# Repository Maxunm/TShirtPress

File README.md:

# See [Rumel.IO](https://www.rumel.io/2019/11/05/T-Shirt-Press/)

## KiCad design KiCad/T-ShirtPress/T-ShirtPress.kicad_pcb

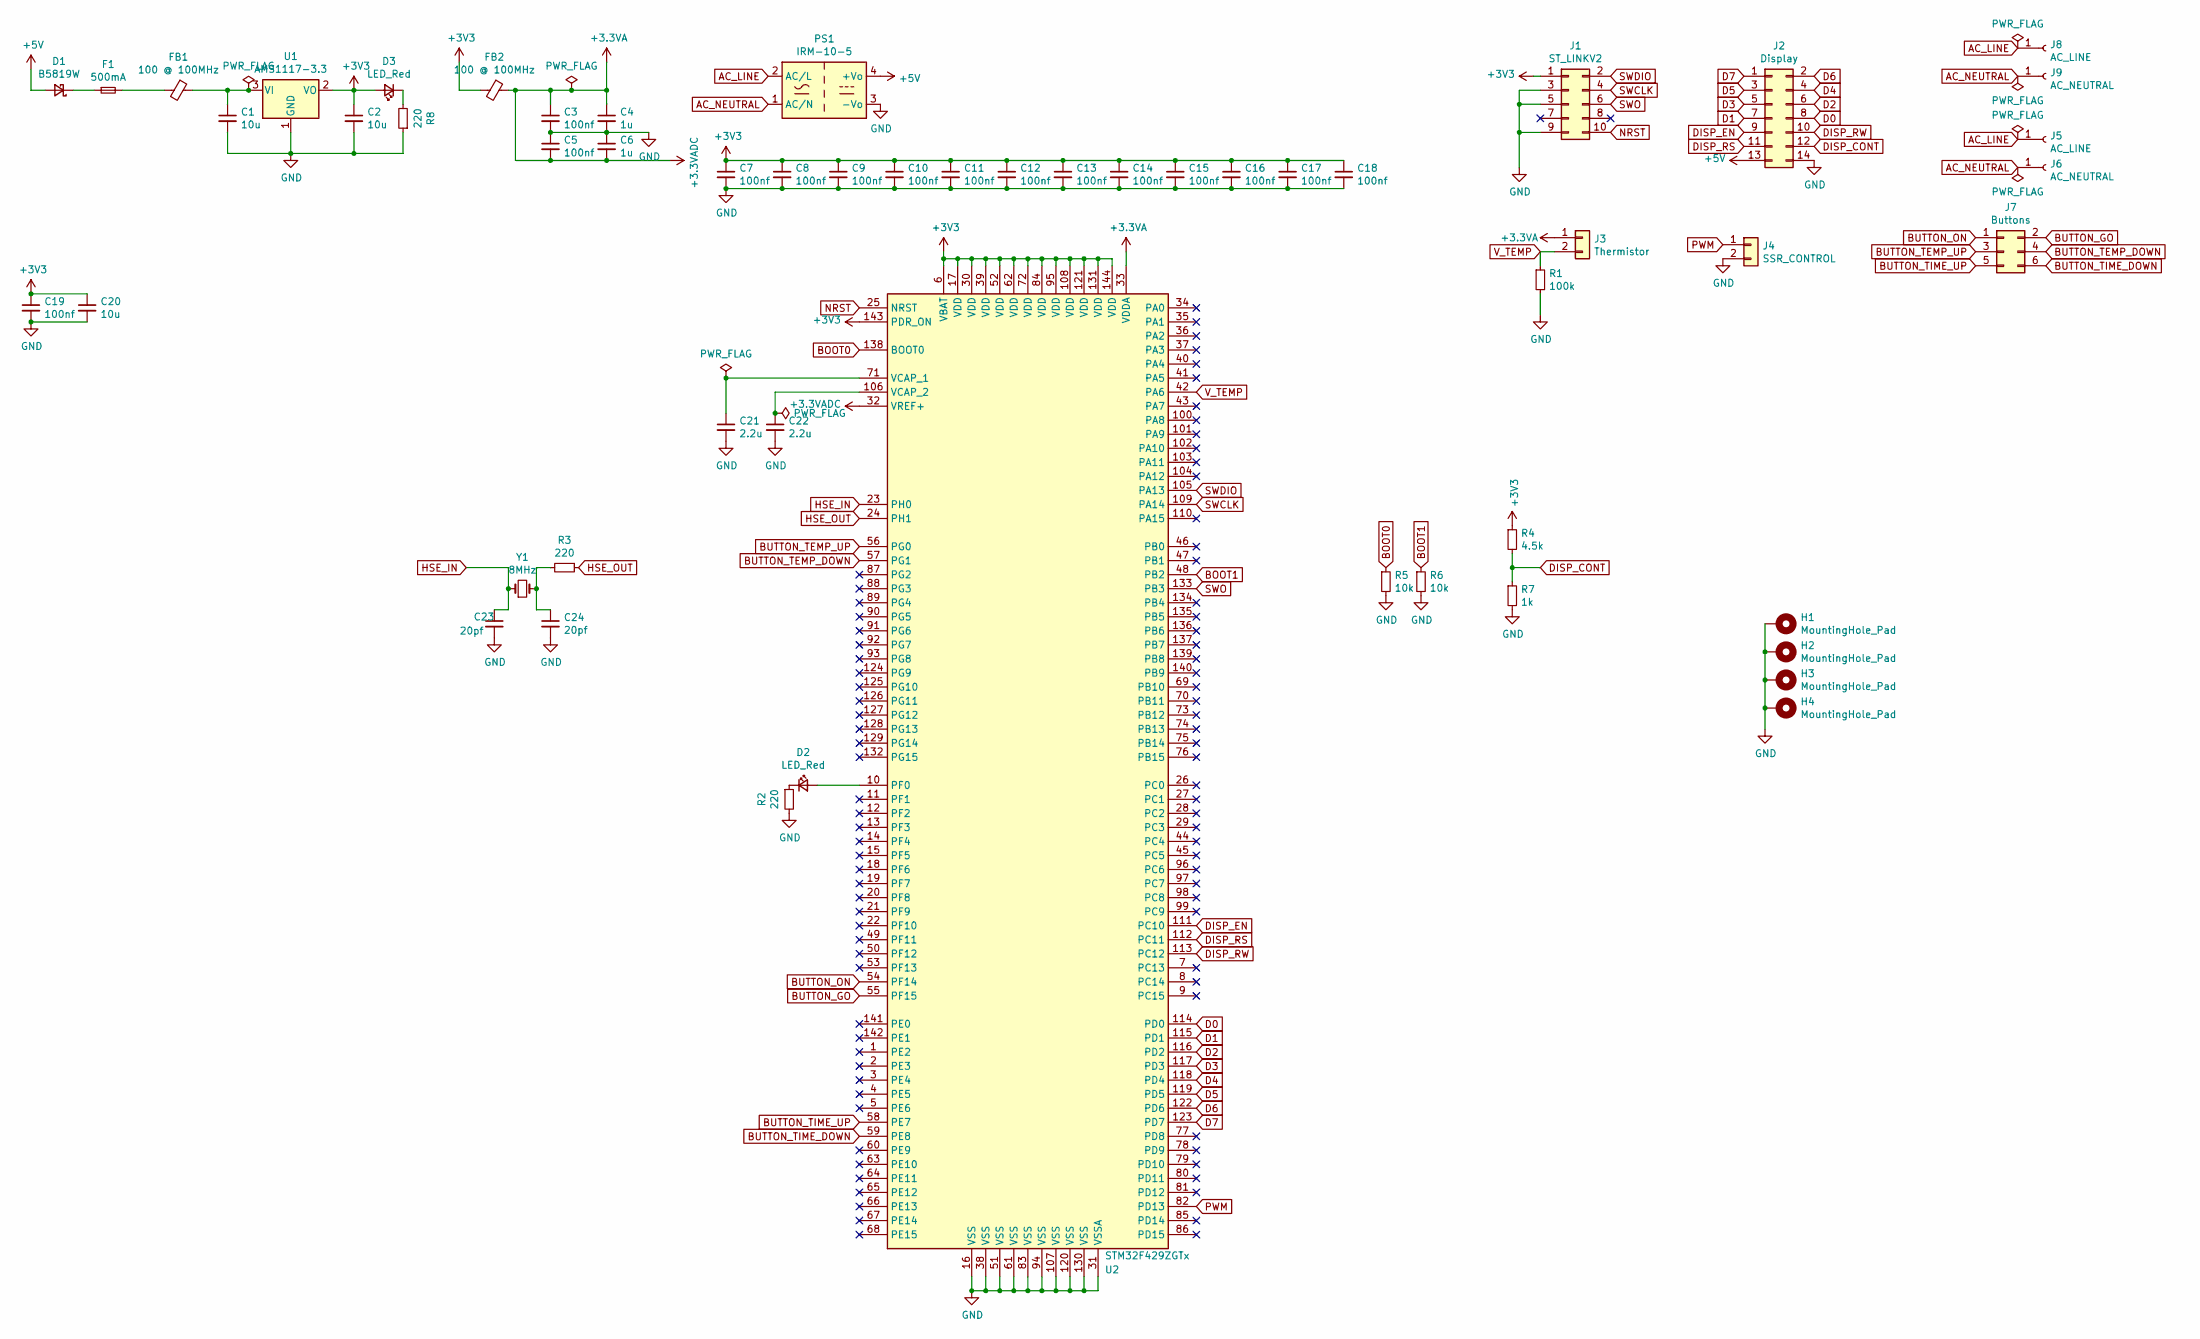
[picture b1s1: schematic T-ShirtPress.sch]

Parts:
C1, C2: 10u; C_0805_2012Metric
C3, C5, C7, C8, C9, C10, C11, C12, C13, C14, C15, C16, C17, C18, C19: 100nf; C_0402_1005Metric
C4, C6: 1u; C_0402_1005Metric
C20: 10u; C_0603_1608Metric
C21, C22: 2.2u; C_0603_1608Metric
C23, C24: 20pf; C_0402_1005Metric
D1: B5819W; D_SOD-123
D2, D3: LED_Red; LED_0603_1608Metric
F1: 500mA; Fuse_1206_3216Metric
FB1, FB2: 100 @ 100MHz; L_0805_2012Metric
H1, H2, H3, H4: MountingHole_Pad; MountingHole_4mm_Pad_Via
J1: ST_LINKV2; PinHeader_2x05_P1.27mm_Vertical_SMD
J2: Display; PinHeader_2x07_P2.54mm_Vertical
J3: Thermistor; JST_EH_B2B-EH-A_1x02_P2.50mm_Vertical
J4: SSR_CONTROL; JST_EH_B2B-EH-A_1x02_P2.50mm_Vertical
J5, J8: AC_LINE; SolderWire-2.5sqmm_1x01_D2.4mm_OD3.6mm
J6, J9: AC_NEUTRAL; SolderWire-2.5sqmm_1x01_D2.4mm_OD3.6mm
J7: Buttons; PinHeader_2x03_P2.54mm_Vertical
PS1: IRM-10-5; Converter_ACDC_MeanWell_IRM-10-xx_THT
R1: 100k; R_0805_2012Metric
R2, R3, R8: 220; R_0603_1608Metric
R4: 4.5k; R_Axial_DIN0204_L3.6mm_D1.6mm_P5.08mm_Horizontal
R5, R6: 10k; R_0402_1005Metric
R7: 1k; R_1206_3216Metric
U1: AMS1117-3.3; SOT-223-3_TabPin2
U2: STM32F429ZGTx; LQFP-144_20x20mm_P0.5mm
Y1: 8MHz; Crystal_SMD_5032-2Pin_5.0x3.2mm

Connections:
+3.3VA: C3.1, C4.1, C5.2, C6.2, FB2.1, J3.1, U2.32 (VREF+), U2.33 (VDDA)
+3V3: C2.1, C7.1, C8.1, C9.1, C10.1, C11.1, C12.1, C13.1, C14.1, C15.1, C16.1, C17.1, C18.1, C19.1, C20.1, D3.2 (A), FB2.2, J1.1, R4.1, U1.2 (VO), U2.6 (VBAT), U2.17 (VDD), U2.30 (VDD), U2.39 (VDD), U2.52 (VDD), U2.62 (VDD), U2.72 (VDD), U2.84 (VDD), U2.95 (VDD), U2.108 (VDD), U2.121 (VDD), U2.131 (VDD), U2.143 (PDR_ON), U2.144 (VDD); also elsewhere on the board
+5V: D1.2 (A), J2.13, PS1.4 (+Vo); also elsewhere on the board
AC_LINE: J5.1, J8.1, PS1.2 (AC/L); also elsewhere on the board
AC_NEUTRAL: J6.1, J9.1, PS1.1 (AC/N); also elsewhere on the board
BOOT0: R5.1, U2.138 (BOOT0)
BOOT1: R6.1, U2.48 (PB2)
BUTTON_GO: J7.2, U2.55 (PF15)
BUTTON_ON: J7.1, U2.54 (PF14)
BUTTON_TEMP_DOWN: J7.4, U2.57 (PG1)
BUTTON_TEMP_UP: J7.3, U2.56 (PG0)
BUTTON_TIME_DOWN: J7.6, U2.59 (PE8)
BUTTON_TIME_UP: J7.5, U2.58 (PE7)
D0: J2.8, U2.114 (PD0)
D1: J2.7, U2.115 (PD1)
D2: J2.6, U2.116 (PD2)
D3: J2.5, U2.117 (PD3)
D4: J2.4, U2.118 (PD4)
D5: J2.3, U2.119 (PD5)
D6: J2.2, U2.122 (PD6)
D7: J2.1, U2.123 (PD7)
DISP_CONT: J2.12, R4.2, R7.1
DISP_EN: J2.9, U2.111 (PC10)
DISP_RS: J2.11, U2.112 (PC11)
DISP_RW: J2.10, U2.113 (PC12)
GND: C1.2, C2.2, C3.2, C4.2, C5.1, C6.1, C7.2, C8.2, C9.2, C10.2, C11.2, C12.2, C13.2, C14.2, C15.2, C16.2, C17.2, C18.2, C19.2, C20.2, C21.2, C22.2, C23.2, C24.2, H1.1, H2.1, H3.1, H4.1, J1.3, J1.5, J1.9, J2.14, J4.2, PS1.3 (-Vo), R1.2, R2.2, R5.2, R6.2, R7.2, R8.1, U1.1 (GND), U2.16 (VSS), U2.31 (VSSA), U2.38 (VSS), U2.51 (VSS), U2.61 (VSS), U2.83 (VSS), U2.94 (VSS), U2.107 (VSS), U2.120 (VSS), U2.130 (VSS); also elsewhere on the board
HSE_IN: C23.1, U2.23 (PH0), Y1.1
HSE_OUT: R3.1, U2.24 (PH1)
NRST: J1.10, U2.25 (NRST)
unnamed: C1.1, FB1.1, U1.3 (VI)
unnamed: C21.1, U2.71 (VCAP_1)
unnamed: C22.1, U2.106 (VCAP_2)
unnamed: C24.1, R3.2, Y1.2
unnamed: D1.1 (K), F1.1
unnamed 34: D2.1 (K), R2.1; also elsewhere on the board
unnamed 35: D2.2 (A), U2.10 (PF0); also elsewhere on the board
unnamed 36: D3.1 (K), R8.2; also elsewhere on the board
unnamed: F1.2, FB1.2
PWM: J4.1, U2.82 (PD13)
SWCLK: J1.4, U2.109 (PA14)
SWDIO: J1.2, U2.105 (PA13)
SWO: J1.6, U2.133 (PB3)
V_TEMP: J3.2, R1.1, U2.42 (PA6)

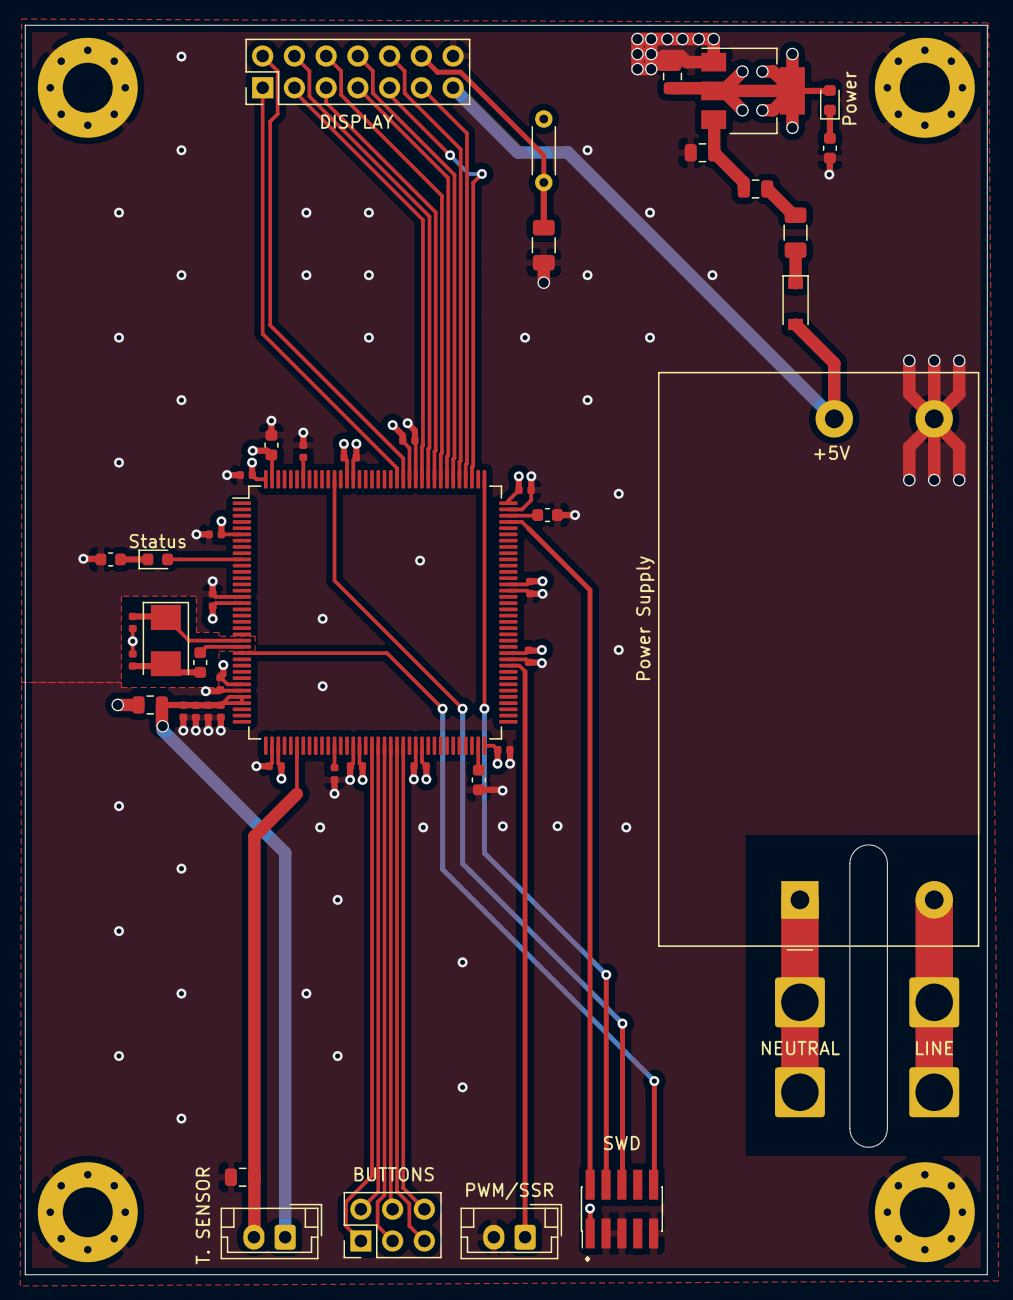
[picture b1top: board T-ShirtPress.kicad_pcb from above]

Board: 4 copper layers, 77.0 x 100.0 mm, 55 parts (0 on the bottom side), 43 nets.

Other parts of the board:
LINE: AC_LINE; SolderWire-2.5sqmm_1x01_D2.4mm_OD3.6mm
NEUTRAL: AC_NEUTRAL; SolderWire-2.5sqmm_1x01_D2.4mm_OD3.6mm
Power: LED_Red; LED_0603_1608Metric
Power Supply: IRM-10-5; Converter_ACDC_MeanWell_IRM-10-xx_THT
Status: LED_Red; LED_0603_1608Metric

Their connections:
+3V3: Power.2; also elsewhere on the board
+5V: Power Supply.4; also elsewhere on the board
AC_LINE: LINE.1, Power Supply.2; also elsewhere on the board
AC_NEUTRAL: NEUTRAL.1, Power Supply.1; also elsewhere on the board
GND: Power Supply.3; also elsewhere on the board
unnamed 34: Status.1; also elsewhere on the board
unnamed 35: Status.2; also elsewhere on the board
unnamed 36: Power.1; also elsewhere on the board

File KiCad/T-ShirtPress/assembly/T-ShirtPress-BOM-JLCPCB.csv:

Designator,Quantity,Value,Footprint,LCSC Part #
"C1, C2, ",2,10u,805,C15850
"C3, C5, C7, C8, C9, C10, C11, C12, C13, C14, C15, C16, C17, C18, C19, ",15,100nf,402,C1525
"C4, C6, ",2,1u,402,C52923
"C20, ",1,10u,603,C19702
"C21, C22, ",2,2.2u,603,C23630
"C23, C24, ",2,20pf,402,C32949
"D1, ",1,B5819W,SOD-123,C8598
"D2, D3, ",2,Red,603,C2286
"FB1, FB2, ",2,100 @ 100MHz,805,C1015
"R1, ",1,100k,805,C17407
"R2, R3, R8, ",3,220,603,C22962
"R5, R6, ",2,10k,402,C25744
"R7, ",1,1k,1206,C4410
"U1, ",1,AMS1117-3.3,SOT-223-3,C6186
"U2, ",1,STM32F429ZGTx,LQFP-144_20.0x20.0x0.5P,C46525
"Y1, ",1,8MHz,SMD-5032_2P,C115962

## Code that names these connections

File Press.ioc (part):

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Mcu.Name=STM32F429ZITx
Mcu.Package=LQFP144
Mcu.UserName=STM32F429ZITx
PA13.Mode=Trace_Asynchronous_SW
PA13.Signal=SYS_JTMS-SWDIO
PA14.Mode=Trace_Asynchronous_SW
PA14.Signal=SYS_JTCK-SWCLK
PA6.Signal=ADCx_IN6
PB3.Mode=Trace_Asynchronous_SW
PB3.Signal=SYS_JTDO-SWO
PC10.GPIOParameters=GPIO_Label
PC10.GPIO_Label=en
PC10.Signal=GPIO_Output
PC11.GPIOParameters=GPIO_Label
PC11.GPIO_Label=rs
PC11.Signal=GPIO_Output
PC12.GPIOParameters=GPIO_Label
PC12.GPIO_Label=rw
PC12.Signal=GPIO_Output
PD0.Signal=GPIO_Output
PD1.Signal=GPIO_Output
PD13.Signal=S_TIM4_CH2
PD2.Signal=GPIO_Output
PD3.Signal=GPIO_Output
PD4.Signal=GPIO_Output
PD5.Signal=GPIO_Output
PD6.Signal=GPIO_Output
PD7.Signal=GPIO_Output
PE7.Signal=GPIO_Input
PE8.Signal=GPIO_Input
PF0.GPIOParameters=GPIO_Label
PF0.GPIO_Label=LED
PF0.Signal=GPIO_Output
PF14.Signal=GPIO_Input
PF15.Signal=GPIO_Input
PG0.Signal=GPIO_Input
PG1.Signal=GPIO_Input
PG13.Signal=GPIO_Output
PH0/OSC_IN.Mode=HSE-External-Oscillator
PH0/OSC_IN.Signal=RCC_OSC_IN
PH1/OSC_OUT.Mode=HSE-External-Oscillator
PH1/OSC_OUT.Signal=RCC_OSC_OUT
RCC.HSE_VALUE=16000000
RCC.SYSCLKFreq_VALUE=100000000
RCC.SYSCLKSource=RCC_SYSCLKSOURCE_PLLCLK
board=custom

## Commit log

2019-11-08 Initializing repository
    This is the progress that I had made before putting this project on GitHub
2019-11-08 Wrote temp conversion code
    The temperature conversion code should take in the ADC value received by the microcontroller and convert it to all three usable temps.
2019-11-08 Final commit tonight
2019-11-08 Files just changed from opening the project
    May have to look into having a git ignore more properly set up in the future
2019-11-08 CubeMX broke things on my other computer
2019-11-12 Updated to include basic PID calculation
    Will need to further change to remove integral wind up and add a low pass filter to filter the noise for the derivative term.
2019-11-12 PID Implemented
    PID is now implemented and works as intended, the solid state relay needed a much slower carrier frequency for the PWM signal so the prescaller was set to 7. PID tuning is what needs to happen next.
2019-11-21 Small changes
2019-11-21 STM32F103
    Re-based to new architecture
2020-01-09 Actively working, needs a PID tune
2020-01-15 Added eagle files
2020-01-16 Added parts to schematic
    Added STM32F429ZIT6 which I used for development and will be using for the bard that is created in this pcb. I most likely will be using the pcb assembly services of something like JLCPCB because I p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
2020-01-16 Updated schematic
2020-02-03 Added Fusion files
    These files are the design for the "product" that is the T-Shirt Press
2020-02-03 More Schematic updates
    Just working on the schematic. Trying to double check all the power electronics. Will likely get design looked over by a peer after it is designed.
2020-02-04 Enabled SWD and updated symbols on schematic
2020-05-28 Rough placement on pcb & Migrate to KiCAD
    I've now roughly placed all the components on the pcb and will work on fine adjustment and routing in the next commit. I've also migrated to KiCAD, the workflow works slightly nicer for how I work be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
2020-05-29 PCB Done!
    The pcb should be done now and it is ordered with assembly so hopefully everything goes well and it will arrive in roughly a week.
2020-06-03 Worked out BOMs
    I seperated the BOMs into three csvs now. One being the parts I ordered from Digikey, one for assebly from JLCPCB and one is just the raw output from KiCAD
2020-07-02 Fixed error with PCB layout
2020-07-02 Re-based project to STM32F429ZGTx
    I also removed then unused files and will end up merging this branch back into master eventually when I'm satisfied that everything is working correctly with the transition.
2020-07-02 Files did not stage correctly
2020-07-02 Updated gerbers to reflect error in PCB
2020-07-02 Added a board verification program
    This program will verify the outputs of the board to insure that all of the pins are timed and working correctly. Use a STLink with SWO enabled to run the program and watch the input from ADC while h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
2020-07-02 Continued writing board verification program
2020-07-12 Got board verification working. Some weird bugs on my laptop.
2020-07-12 Working mockup of press.
    Going to try out the current settings for the press that are outlined in this code. While trying to tune the PID by hand I ended with a kP value of 5000 and the other two set to 0 for the time being.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
2020-11-19 Accidentially added senior design files here
